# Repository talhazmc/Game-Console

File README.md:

# Game-Console
STM32 based game console PCB design with OLED display, buttons, buzzer, and 555 timer circuit.

# STM32 Game Console PCB Design

This repository contains my custom STM32-based mini game console PCB project designed with KiCad.

The project was developed as a compact embedded system board that combines an STM32 microcontroller module, OLED display, push buttons, buzzer, LEDs, and a 555 timer circuit on a custom PCB.

---

## Project Overview

The main purpose of this project was to design and build a small game console / gamepad-style embedded system board.

The board includes directional buttons, A/B action buttons, an OLED display for menu and game output, a buzzer for sound feedback, LEDs for visual indicators, and an STM32 module as the main controller.

The PCB was designed in KiCad, manufactured as a custom red PCB, assembled with through-hole and module-based components, and tested as a functional hardware prototype.

---

## PCB Layout

The PCB layout was created in KiCad.

The design includes the STM32 module on the right side, user control buttons on the left and bottom sections, an OLED display area, buzzer, LED indicators, and a separate 555 timer circuit section.

---

## 3D PCB View

The 3D view was used to check the physical placement of the components before manufacturing.

This step helped verify the button positions, display area, STM32 module placement, buzzer location, mounting holes, and overall board appearance.

---

## Manufactured PCB

After completing the PCB design, the board was manufactured with a red solder mask.

The silkscreen includes component references, button labels, STM32 pin names, and custom graphics such as the “Game Over” text, skull icon, and pixel-style game icons.

---

## Assembled Prototype

The components were soldered onto the manufactured PCB, including the STM32 module, OLED display, buzzer, LEDs, push buttons, resistors, capacitors, diodes, and 555 timer circuit components.

---

## OLED Menu Test

The OLED display was tested with a simple menu interface.

The menu includes different options such as starting the game, Pong mode, and Tetris mode.

---

## Game Test

The board was also tested with a basic game screen.

The OLED display shows a score value and simple game objects, while the push buttons are used as user controls.

---

## Main Features

- STM32-based mini game console board
- OLED display interface
- Directional control buttons
- A and B action buttons
- Buzzer for sound output
- LED indicators
- 555 timer circuit section
- Custom PCB design
- Manufactured and assembled hardware prototype
- Menu interface and basic game screen test

---

## Main Components

- STM32 microcontroller module
- OLED display module
- Push buttons
- Buzzer
- LEDs
- NE555 timer IC
- Resistors
- Capacitors
- Diodes
- Pin headers
- Custom PCB

---

## Working Principle

The STM32 module acts as the main controller of the system.

The push buttons are used as digital inputs for menu navigation and game control. The OLED display provides visual output such as menu options, score, and game graphics.

The buzzer is used for sound feedback, while LEDs provide visual status indication. The 555 timer circuit section was added as an additional timing / signal generation block on the board.

This project demonstrates how a microcontroller, display, buttons, and basic output components can be combined on a custom PCB to create a small interactive embedded system.

---

## What I Learned

Through this project, I gained practical experience in:

- Designing a custom STM32-based PCB
- Creating a gamepad-style embedded system board
- Using KiCad for PCB layout and 3D visualization
- Working with OLED displays
- Reading multiple push button inputs
- Adding buzzer and LED feedback
- Integrating a 555 timer circuit into a larger PCB
- Preparing a PCB for manufacturing
- Soldering and testing a real hardware prototype

---

## Tools and Technologies

- KiCad
- STM32
- OLED Display
- NE555 Timer
- PCB Design
- Embedded Systems
- Push Button Inputs
- Buzzer Output
- C / C++ Firmware

---

## Author

**Talha Üzümcü**  
Electrical and Electronics Engineer  
GitHub: [talhazmc](https://github.com/talhazmc)

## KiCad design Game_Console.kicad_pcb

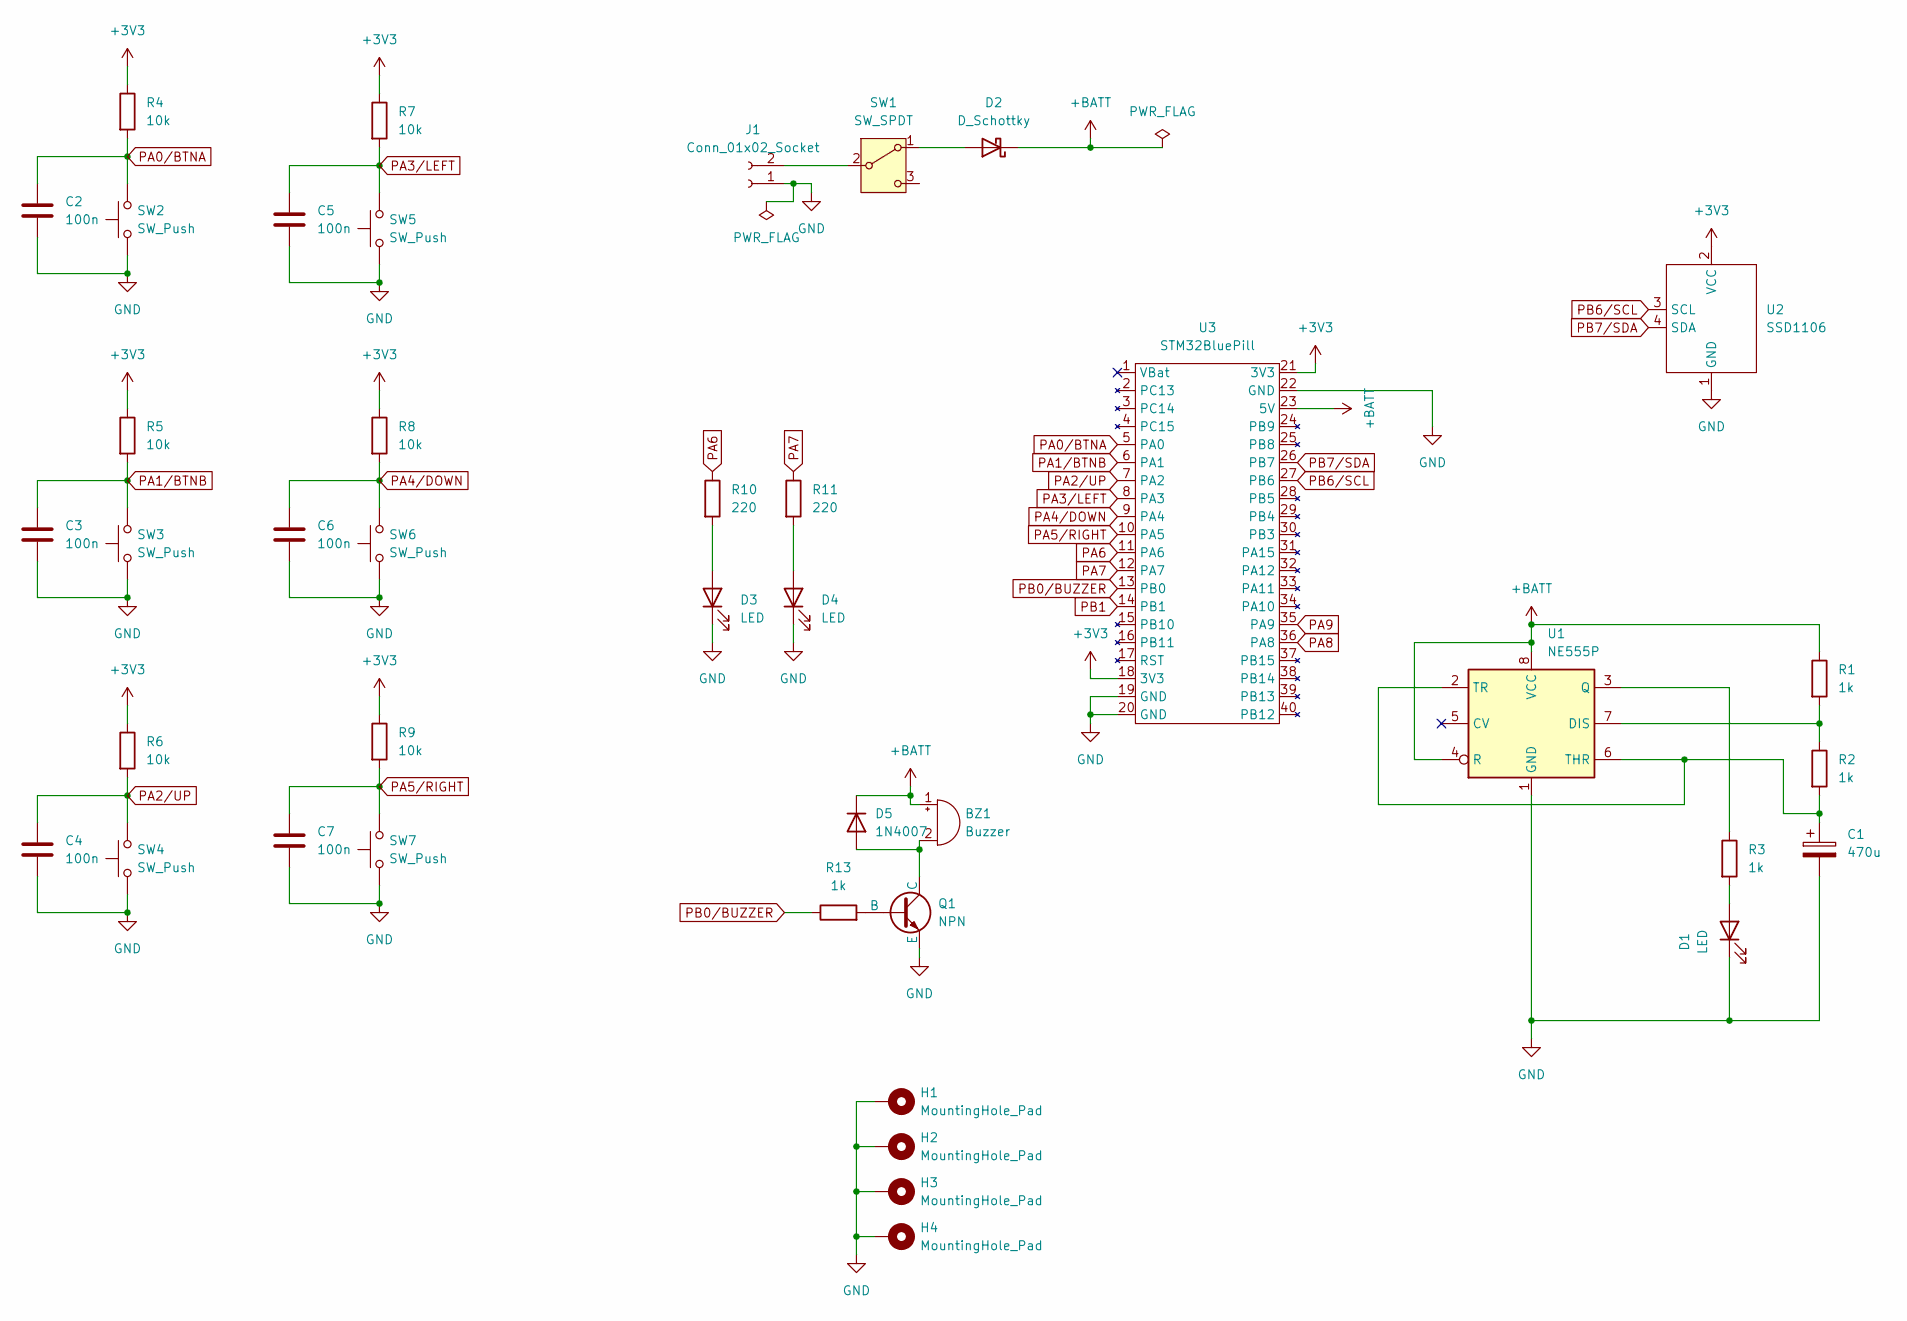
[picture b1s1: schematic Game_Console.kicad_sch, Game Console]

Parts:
BZ1: Buzzer; Buzzer_12x9.5RM7.6
C1: 470u; CP_Radial_D6.3mm_P2.50mm
C2, C3, C4, C5, C6, C7: 100n; C_Disc_D4.7mm_W2.5mm_P5.00mm
D1, D3, D4: LED; LED_D5.0mm
D2: D_Schottky; D_DO-35_SOD27_P7.62mm_Horizontal
D5: 1N4007; D_DO-41_SOD81_P10.16mm_Horizontal
H1, H2, H3, H4: MountingHole_Pad; MountingHole_2.5mm_Pad
J1: Conn_01x02_Socket; Molex_Micro-Latch_53254-0270_1x02_P2.00mm_Horizontal
Q1: NPN; TO-92_Inline
R1, R2, R3, R13: 1k; R_Axial_DIN0207_L6.3mm_D2.5mm_P7.62mm_Horizontal
R4, R5, R6, R7, R8, R9: 10k; R_Axial_DIN0207_L6.3mm_D2.5mm_P7.62mm_Horizontal
R10, R11: 220; R_Axial_DIN0207_L6.3mm_D2.5mm_P7.62mm_Horizontal
SW1: SW_SPDT; Slide_Switch
SW2, SW3, SW4, SW5, SW6, SW7: SW_Push; SW_PUSH_6mm
U1: NE555P; DIP-8_W7.62mm
U2: SSD1106; SSD1106_Module
U3: STM32BluePill

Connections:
+3V3: R4.1, R5.1, R6.1, R7.1, R8.1, R9.1, U2.2 (VCC), U3.18 (3V3), U3.21 (3V3)
+BATT: BZ1.1 (+), D2.1 (K), D5.1 (K), R1.1, U1.4 (R), U1.8 (VCC), U3.23 (5V)
GND: C1.2, C2.2, C3.2, C4.2, C5.2, C6.2, C7.2, D1.1 (K), D3.1 (K), D4.1 (K), H1.1, H2.1, H3.1, H4.1, J1.1, Q1.3 (E), SW2.1, SW3.1, SW4.1, SW5.1, SW6.1, SW7.1, U1.1 (GND), U2.1 (GND), U3.19 (GND), U3.20 (GND), U3.22 (GND)
unnamed: BZ1.2 (-), D5.2 (A), Q1.1 (C)
unnamed: D1.2 (A), R3.2
unnamed: D2.2 (A), SW1.1 (A)
unnamed: D3.2 (A), R10.2
unnamed: D4.2 (A), R11.2
unnamed: J1.2, SW1.2 (B)
unnamed: Q1.2 (B), R13.2
unnamed: R1.2, R2.1, U1.7 (DIS)
unnamed: R3.1, U1.3 (Q)
unnamed: C1.1, R2.2, U1.2 (TR), U1.6 (THR)
PA0/BTNA: C2.1, R4.2, SW2.2, U3.5 (PA0)
PA1/BTNB: C3.1, R5.2, SW3.2, U3.6 (PA1)
PA2/UP: C4.1, R6.2, SW4.2, U3.7 (PA2)
PA3/LEFT: C5.1, R7.2, SW5.2, U3.8 (PA3)
PA4/DOWN: C6.1, R8.2, SW6.2, U3.9 (PA4)
PA5/RIGHT: C7.1, R9.2, SW7.2, U3.10 (PA5)
PA6: R10.1, U3.11 (PA6)
PA7: R11.1, U3.12 (PA7)
PA8: U3.36 (PA8)
PA9: U3.35 (PA9)
PB0/BUZZER: R13.1, U3.13 (PB0)
PB1: U3.14 (PB1)
PB6/SCL: U2.3 (SCL), U3.27 (PB6)
PB7/SDA: U2.4 (SDA), U3.26 (PB7)

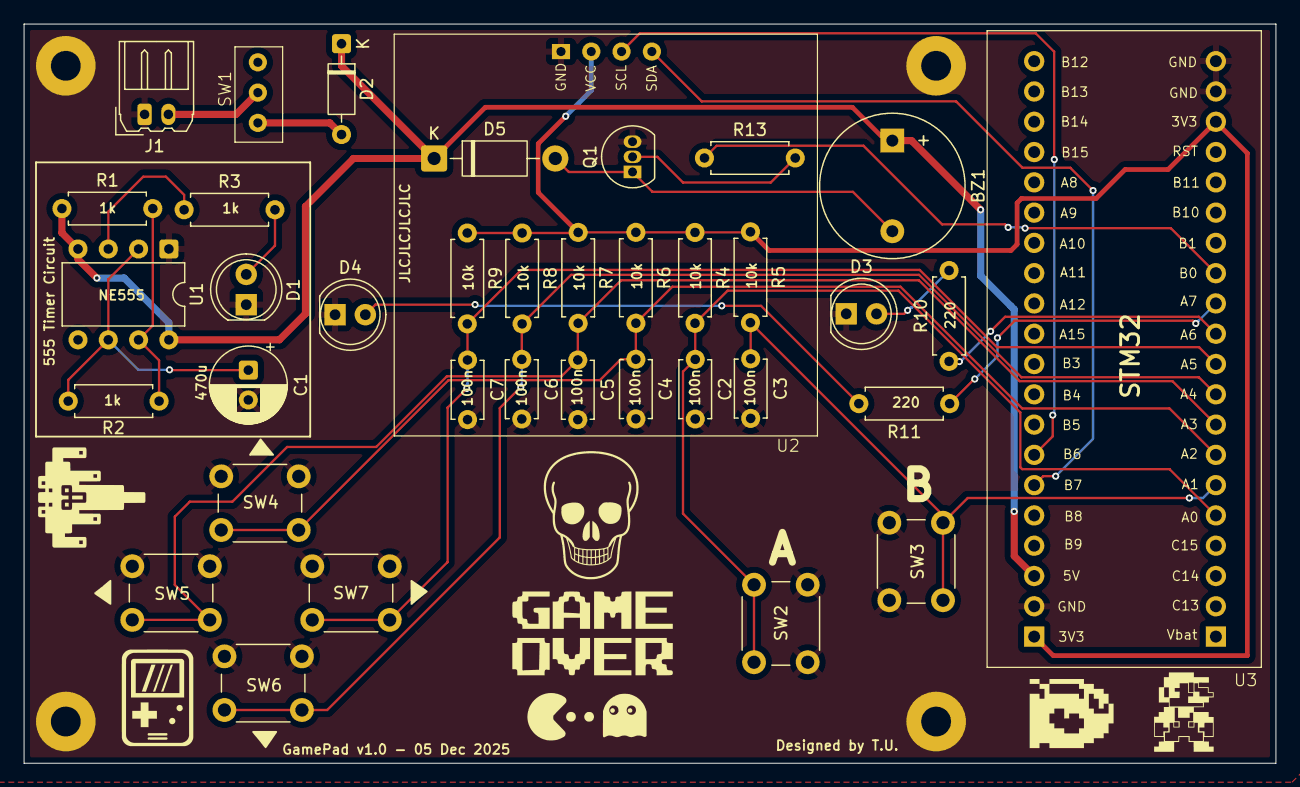
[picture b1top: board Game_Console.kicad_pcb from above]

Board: 4 copper layers, 105.0 x 62.0 mm, 41 parts (0 on the bottom side), 24 nets.

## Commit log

2026-06-29 Enhance README with comprehensive project details
    Expanded the README to provide detailed project information, including project overview, PCB layout, 3D view, manufactured PCB, assembled prototype, OLED menu test, game test, main features, main com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
